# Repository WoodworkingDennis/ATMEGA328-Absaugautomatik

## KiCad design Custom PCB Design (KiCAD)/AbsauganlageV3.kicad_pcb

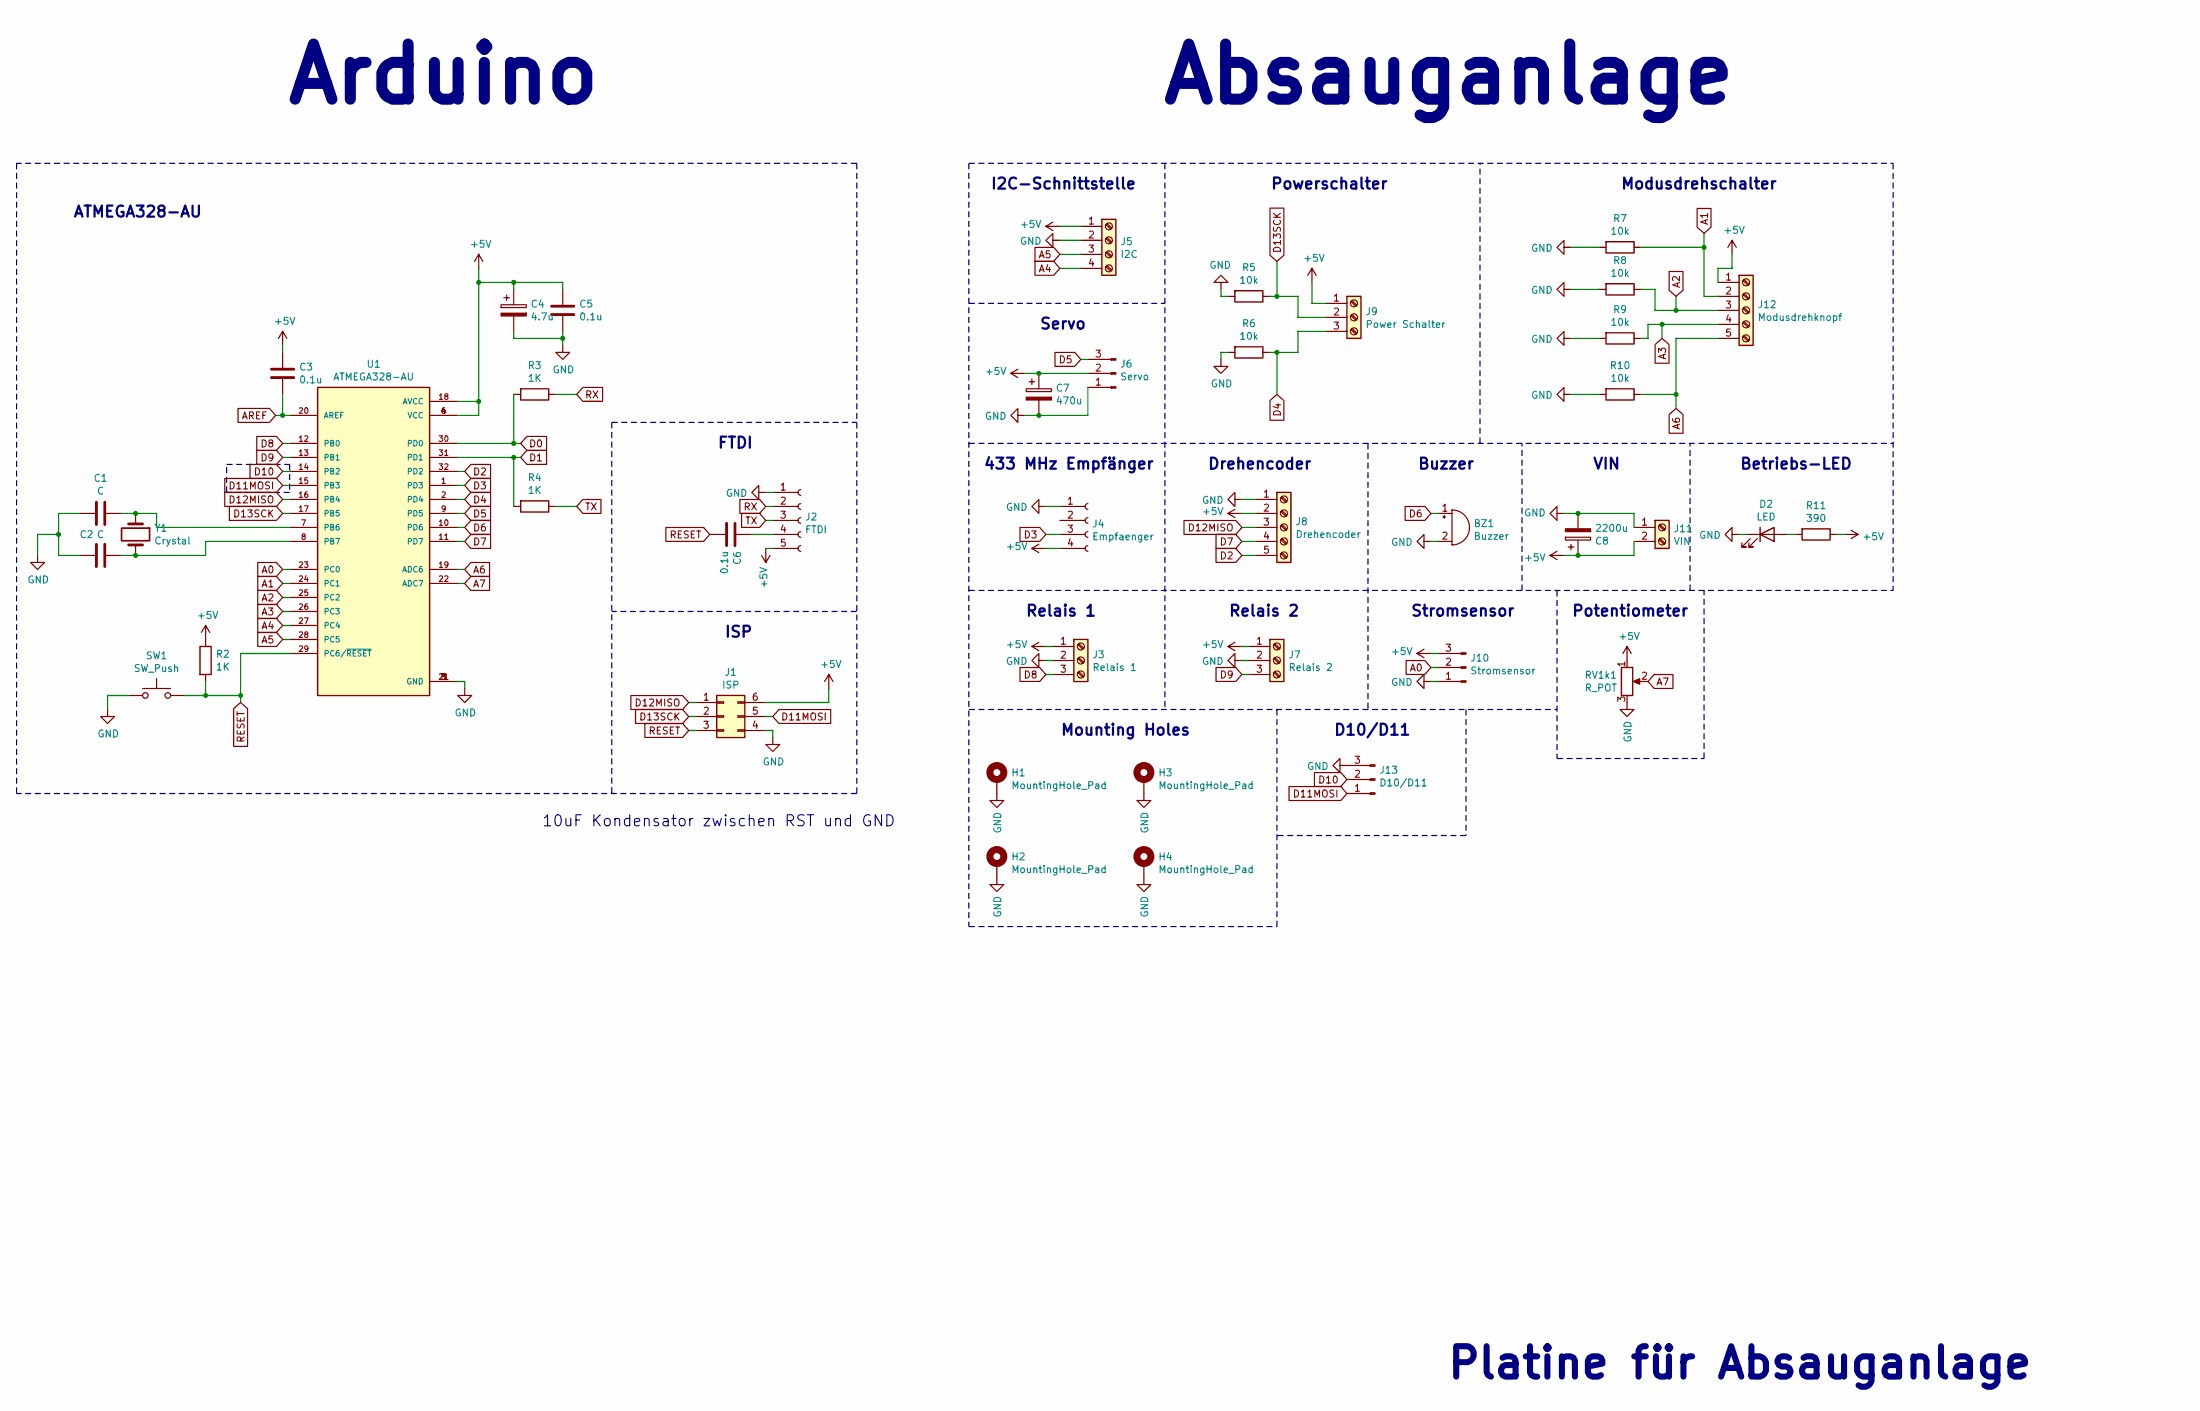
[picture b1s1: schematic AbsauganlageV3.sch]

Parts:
BZ1: Buzzer; Buzzer_12x9.5RM7.6
C1, C2: C; C_Disc_D3.8mm_W2.6mm_P2.50mm
C3, C5, C6: 0.1u; C_Disc_D6.0mm_W2.5mm_P5.00mm
C4: 4.7u; CP_Radial_D4.0mm_P1.50mm
C7: 470u; CP_Radial_D8.0mm_P3.50mm
C8: 2200u; CP_Radial_D10.0mm_P5.00mm
D2: LED; LED_D3.0mm_Clear
H1, H2, H3, H4: MountingHole_Pad; MountingHole_3.2mm_M3_Pad_Via
J1: ISP; PinHeader_2x03_P2.54mm_Vertical
J2: FTDI; PinHeader_1x05_P2.54mm_Vertical
J3: Relais 1; WJ301V-5.0-3P
J4: Empfaenger; PinHeader_1x04_P2.54mm_Vertical
J5: I2C; TE_282834-4
J6: Servo; PinHeader_1x03_P2.54mm_Vertical
J7: Relais 2; WJ301V-5.0-3P
J8: Drehencoder; TE_282834-5
J9: Power Schalter; TE_282834-3
J10: Stromsensor; PinHeader_1x03_P2.54mm_Vertical
J11: VIN; WJ301V-5.0-2P
J12: Modusdrehknopf; TE_282834-5
J13: D10/D11; PinHeader_1x03_P2.54mm_Vertical
R2, R3, R4: 1K; R_Axial_DIN0207_L6.3mm_D2.5mm_P7.62mm_Horizontal
R5, R6, R7, R8, R9, R10: 10k; R_Axial_DIN0207_L6.3mm_D2.5mm_P7.62mm_Horizontal
R11: 390; R_Axial_DIN0207_L6.3mm_D2.5mm_P7.62mm_Horizontal
RV1k1: R_POT; Potentiometer_silver_naked
SW1: SW_Push; TS-1187A-B-A-B
U1: ATMEGA328-AU; QFP80P900X900X120-32N
Y1: Crystal; Crystal_HC49-U_Vertical

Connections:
+5V: C3.1, C4.1, C5.1, C7.1, C8.1, J1.6, J2.5, J3.1, J4.4, J5.1, J6.2, J7.1, J8.2, J9.1, J10.3, J11.2, J12.1, R2.1, R11.1, RV1k1.1, U1.4 (VCC), U1.6 (VCC), U1.18 (AVCC)
A0: J10.2, U1.23 (PC0)
A1: J12.2, R7.1, U1.24 (PC1)
A2: J12.3, R8.1, U1.25 (PC2)
A3: J12.4, R9.1, U1.26 (PC3)
A4: J5.4, U1.27 (PC4)
A5: J5.3, U1.28 (PC5)
A6: J12.5, R10.1, U1.19 (ADC6)
A7: RV1k1.2, U1.22 (ADC7)
AREF: C3.2, U1.20 (AREF)
D0: R3.2, U1.30 (PD0)
D1: R4.2, U1.31 (PD1)
D2: J8.5, U1.32 (PD2)
D3: J4.3, U1.1 (PD3)
D4: J9.3, R6.1, U1.2 (PD4)
D5: J6.3, U1.9 (PD5)
D6: BZ1.1 (-), U1.10 (PD6)
D7: J8.4, U1.11 (PD7)
D8: J3.3, U1.12 (PB0)
D9: J7.3, U1.13 (PB1)
D10: J13.2, U1.14 (PB2)
D11MOSI: J1.5, J13.1, U1.15 (PB3)
D12MISO: J1.1, J8.3, U1.16 (PB4)
D13SCK: J1.2, J9.2, R5.1, U1.17 (PB5)
GND: BZ1.2 (+), C1.2, C2.2, C4.2, C5.2, C7.2, C8.2, D2.1 (K), H1.1, H2.1, H3.1, H4.1, J1.4, J2.1, J3.2, J4.1, J5.2, J6.1, J7.2, J8.1, J10.1, J11.1, J13.3, R5.2, R6.2, R7.2, R8.2, R9.2, R10.2, RV1k1.3, SW1.1, U1.3 (GND), U1.5 (GND), U1.21 (GND); also elsewhere on the board
unnamed: C1.1, U1.7 (PB6), Y1.1
unnamed: C2.1, U1.8 (PB7), Y1.2
unnamed: C6.1, J2.4
unnamed: D2.2 (A), R11.2
RESET: C6.2, J1.3, R2.2, SW1.2, U1.29 (PC6/~RESET); also elsewhere on the board
RX: J2.2, R3.1
TX: J2.3, R4.1

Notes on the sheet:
Arduino
I2C-Schnittstelle
Powerschalter
Modusdrehschalter
Absauganlage
Servo
433 MHz Empfänger
Drehencoder
Buzzer
VIN
Betriebs-LED
Relais 1
Relais 2
Platine für Absauganlage
Stromsensor
Potentiometer
Mounting Holes
FTDI
ISP
ATMEGA328-AU
D10/D11
10uF Kondensator zwischen RST und GND

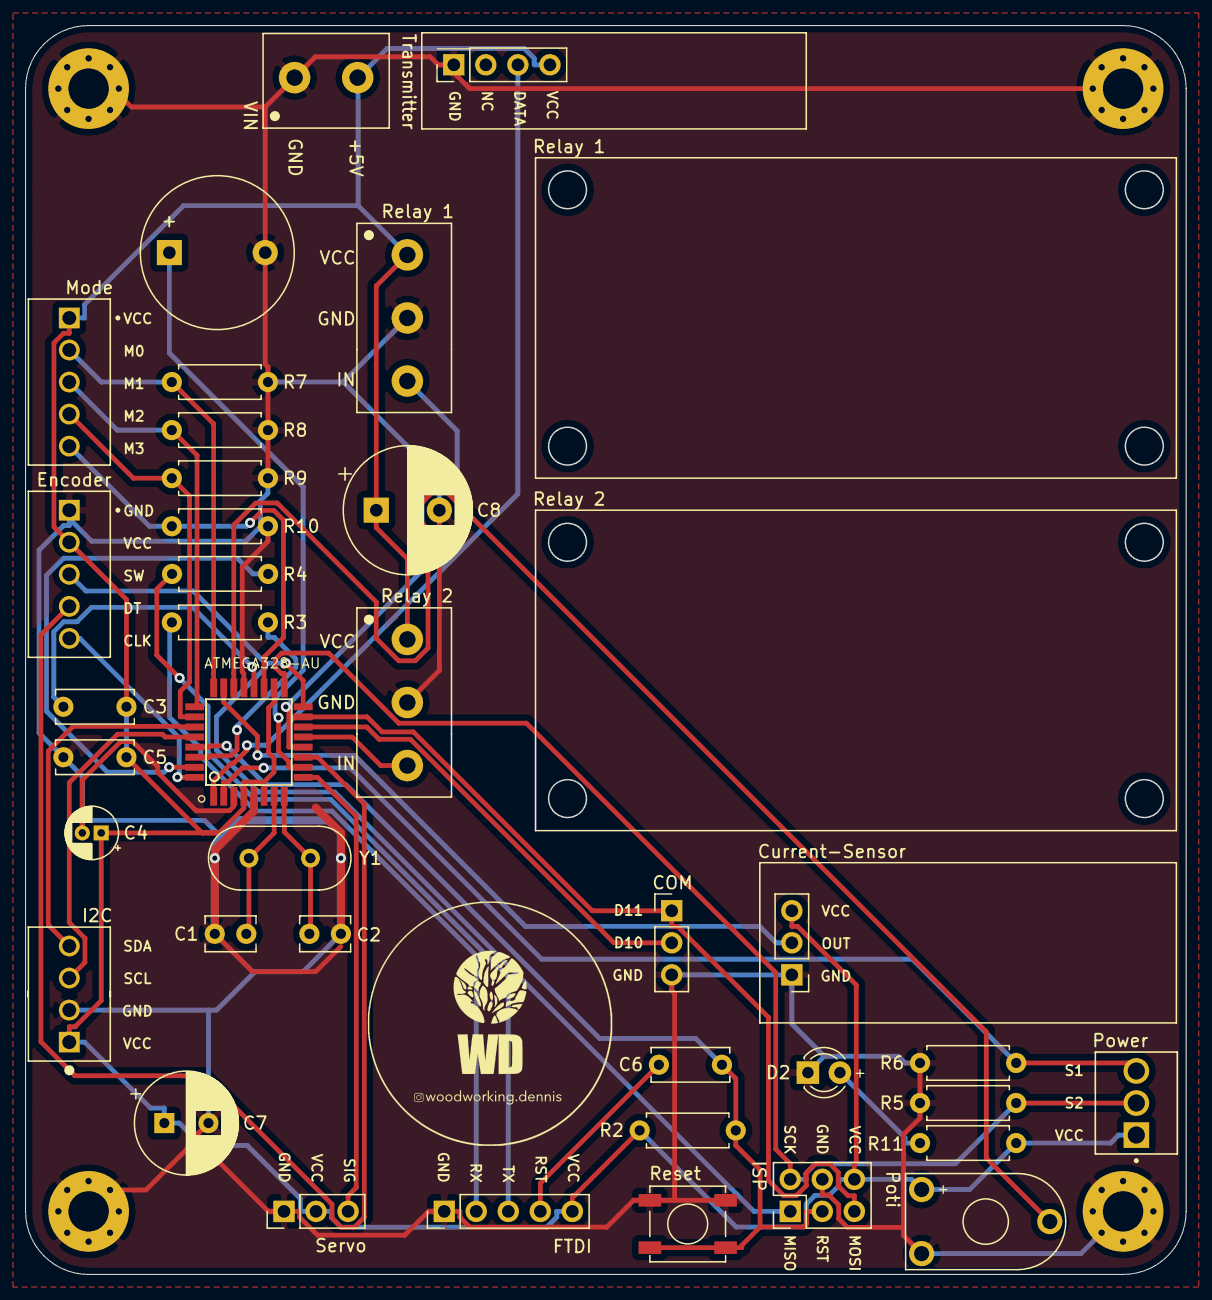
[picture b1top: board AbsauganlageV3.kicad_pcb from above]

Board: 2 copper layers, 91.9 x 98.9 mm, 43 parts (1 on the bottom side), 32 nets.

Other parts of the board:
G1: LOGO; woodworking-dennis-22x22
G2: LOGO; woodworking-dennis-40x40
Reset: SW_Push; TS-1187A-B-A-B

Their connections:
GND: Reset.1; also elsewhere on the board
RESET: Reset.2; also elsewhere on the board
